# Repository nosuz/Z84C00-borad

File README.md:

# Z80(Z84C00) CPU board

This board is designed for running CP/M.

|Item|Spec|
|:--|:--|
|CPU|Z84C00|
|Memory Size|128KiB|
|CPU Clock|Max. 14MHz|
|Interface|USB|

The USB port is used as a interface to connect with the subsystem that controles a console and disk drives.

|File name|Contents|
|:---------|:---|
|Z8S180.pdf|Circuit drawing(PDF)|
|Z8S180.xlsx|BOM list(Excel)|
|Z8S180.zip|zipped Gerber files|

## References

[Z80マイコンボードの製作](https://tech.nosuz.jp/2016/08/z80-cpu-borad/)

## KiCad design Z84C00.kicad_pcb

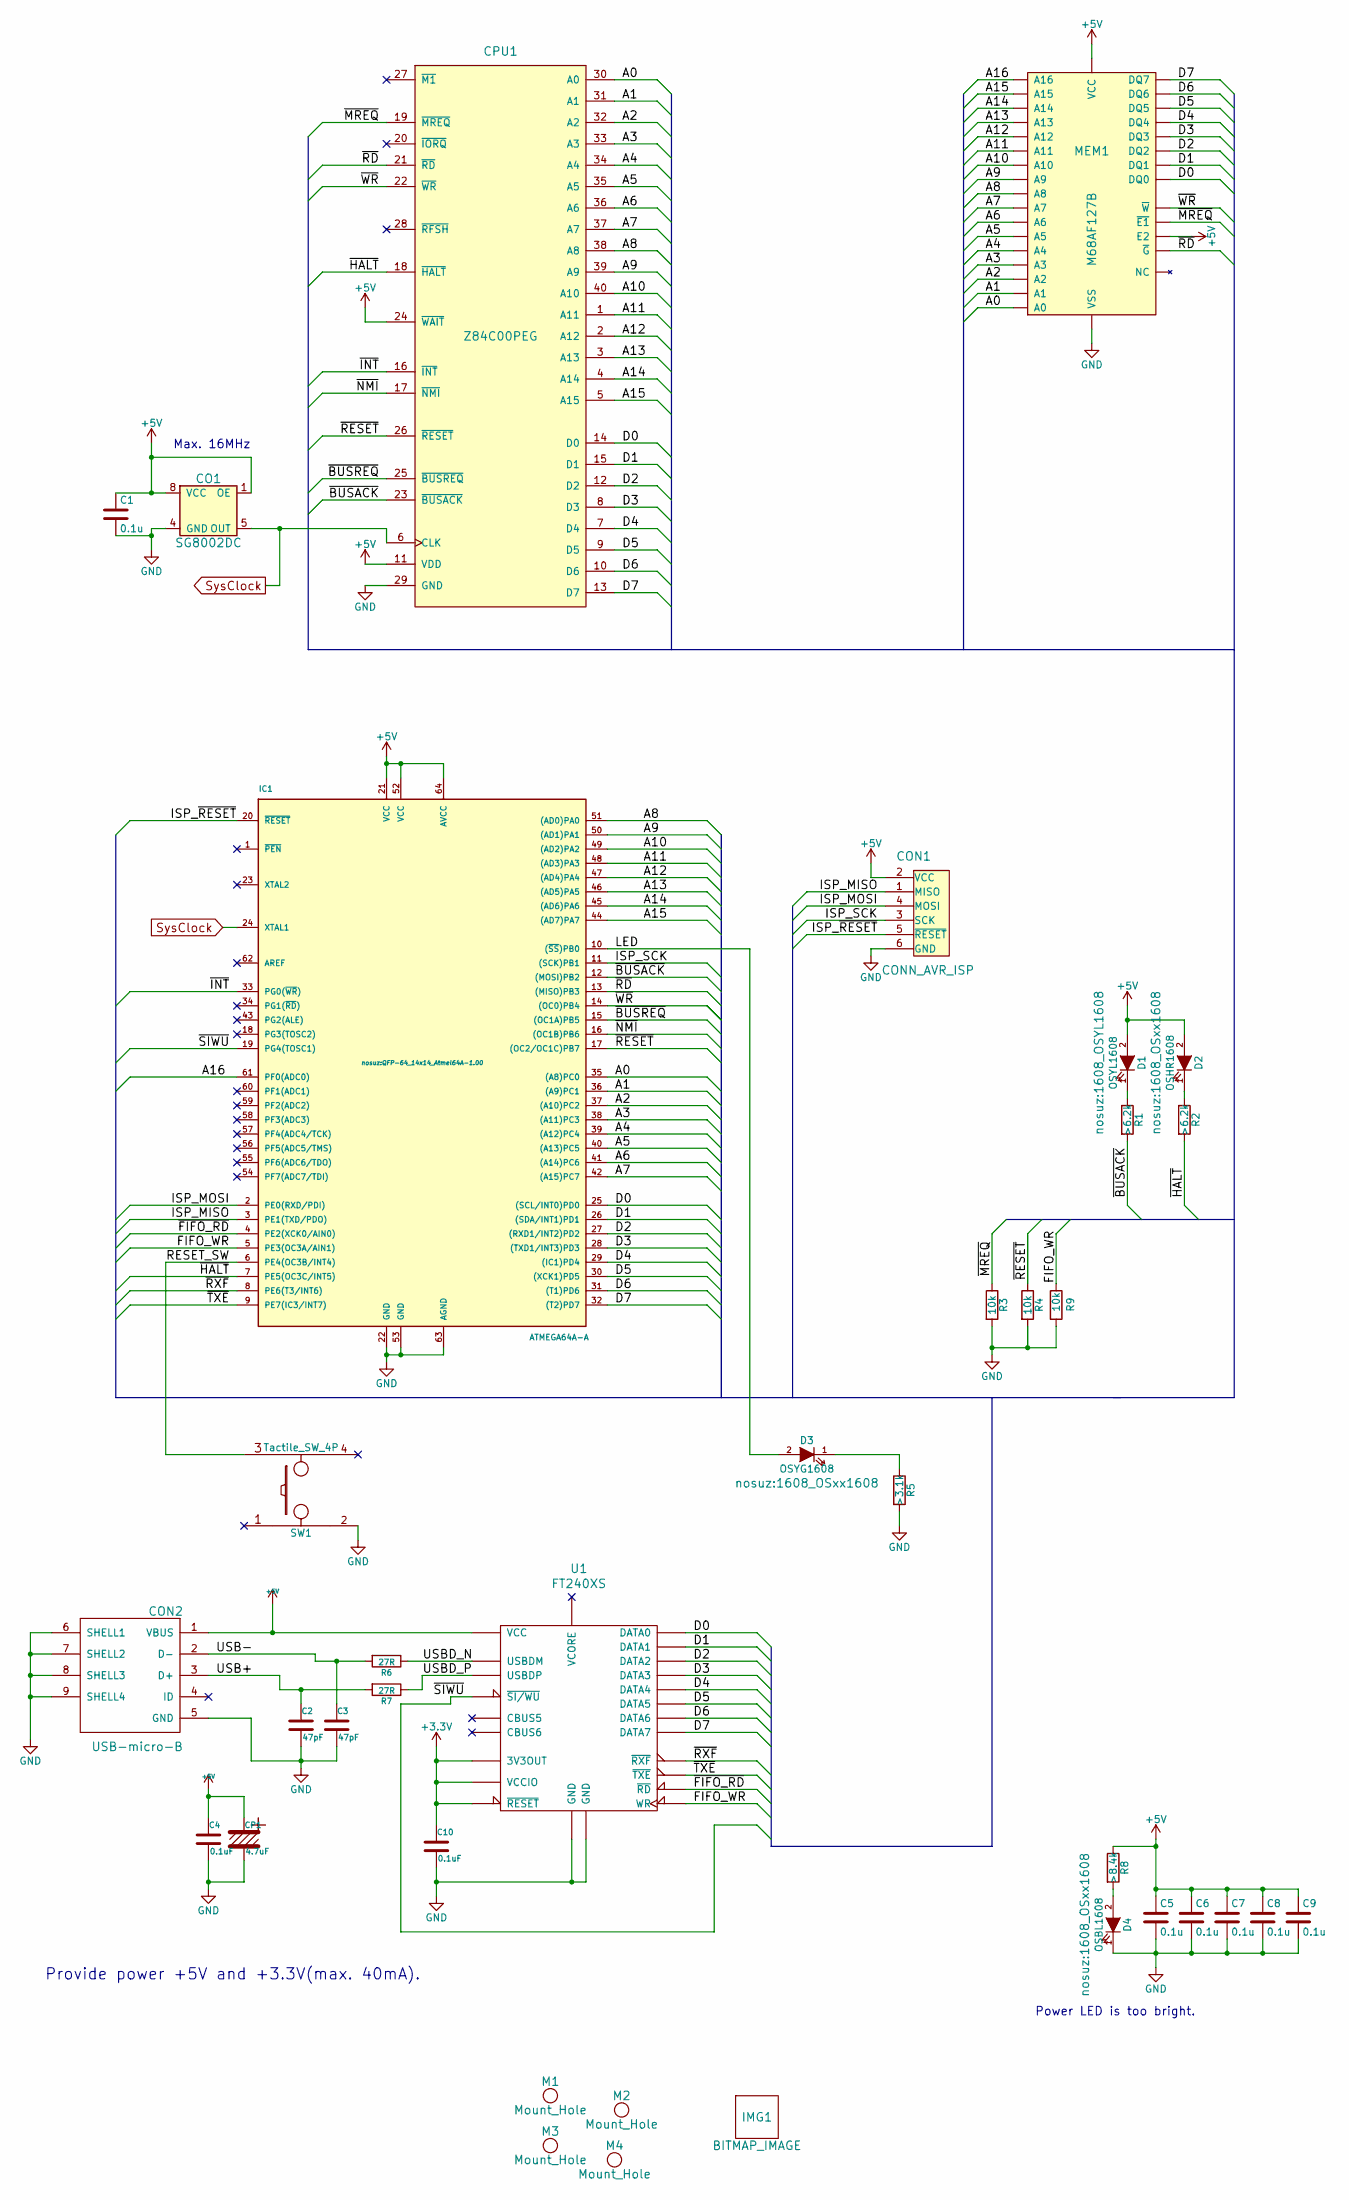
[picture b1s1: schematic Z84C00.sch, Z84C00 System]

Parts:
C1, C5, C6, C7, C8, C9: 0.1u; C_2012
C2, C3: 47pF; C_2012
C4, C10: 0.1uF; C_2012
CO1: SG8002DC; DIP8_2227MC-08
CON1: CONN_AVR_ISP; AVR_ISP_2x03
CON2: USB-micro-B; USB-micro-B_Hirose
CP1: 4.7uF; CP_SMD_D5
CPU1: Z84C00PEG; DIP-40_Z84C00
D1: OSYL1608; 1608_OSYL1608
D2: OSHR1608; 1608_OSxx1608
D3: OSYG1608; 1608_OSxx1608
D4: OSBL1608; 1608_OSxx1608
IC1: ATMEGA64A-A; QFP-64_14x14_Atmel64A-1.00
IMG1: BITMAP_IMAGE; Icon_Nosuz
M1, M2, M3, M4: Mount_Hole; HOLE-M3
MEM1: M68AF127B; SO32_STM_M68AF127B
R1, R2: >6.2k; R_1608
R3, R4, R9: 10k; R_1608
R5: >3.1k; R_1608
R6, R7: 27R; R_1608
R8: >8.4k; R_1608
SW1: Tactile_SW_4P; SKRPACE010
U1: FT240XS; SSOP-24_FT240XS

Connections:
+3V3: C10.1, U1.3 (VCCIO), U1.15 (3V3OUT), U1.16 (~RESET)
+5V: C1.1, C4.1, C5.1, C6.1, C7.1, C8.1, C9.1, CO1.1 (OE), CO1.8 (VCC), CON1.2 (VCC), CON2.1 (VBUS), CP1.1, CPU1.11 (VDD), CPU1.24 (~WAIT), D1.2 (A), D2.2 (A), IC1.21 (VCC), IC1.52 (VCC), IC1.64 (AVCC), MEM1.30 (E2), MEM1.32 (VCC), R8.1, U1.18 (VCC)
/A0: CPU1.30 (A0), IC1.35 ((A8)PC0), MEM1.12 (A0)
/A1: CPU1.31 (A1), IC1.36 ((A9)PC1), MEM1.11 (A1)
/A2: CPU1.32 (A2), IC1.37 ((A10)PC2), MEM1.10 (A2)
/A3: CPU1.33 (A3), IC1.38 ((A11)PC3), MEM1.9 (A3)
/A4: CPU1.34 (A4), IC1.39 ((A12)PC4), MEM1.8 (A4)
/A5: CPU1.35 (A5), IC1.40 ((A13)PC5), MEM1.7 (A5)
/A6: CPU1.36 (A6), IC1.41 ((A14)PC6), MEM1.6 (A6)
/A7: CPU1.37 (A7), IC1.42 ((A15)PC7), MEM1.5 (A7)
/A8: CPU1.38 (A8), IC1.51 ((AD0)PA0), MEM1.27 (A8)
/A9: CPU1.39 (A9), IC1.50 ((AD1)PA1), MEM1.26 (A9)
/A10: CPU1.40 (A10), IC1.49 ((AD2)PA2), MEM1.23 (A10)
/A11: CPU1.1 (A11), IC1.48 ((AD3)PA3), MEM1.25 (A11)
/A12: CPU1.2 (A12), IC1.47 ((AD4)PA4), MEM1.4 (A12)
/A13: CPU1.3 (A13), IC1.46 ((AD5)PA5), MEM1.28 (A13)
/A14: CPU1.4 (A14), IC1.45 ((AD6)PA6), MEM1.3 (A14)
/A15: CPU1.5 (A15), IC1.44 ((AD7)PA7), MEM1.31 (A15)
/A16: IC1.61 (PF0(ADC0)), MEM1.2 (A16)
/D0: CPU1.14 (D0), IC1.25 ((SCL/INT0)PD0), MEM1.13 (DQ0), U1.24 (DATA0)
/D1: CPU1.15 (D1), IC1.26 ((SDA/INT1)PD1), MEM1.14 (DQ1), U1.4 (DATA1)
/D2: CPU1.12 (D2), IC1.27 ((RXD1/INT2)PD2), MEM1.15 (DQ2), U1.2 (DATA2)
/D3: CPU1.8 (D3), IC1.28 ((TXD1/INT3)PD3), MEM1.17 (DQ3), U1.9 (DATA3)
/D4: CPU1.7 (D4), IC1.29 ((IC1)PD4), MEM1.18 (DQ4), U1.1 (DATA4)
/D5: CPU1.9 (D5), IC1.30 ((XCK1)PD5), MEM1.19 (DQ5), U1.7 (DATA5)
/D6: CPU1.10 (D6), IC1.31 ((T1)PD6), MEM1.20 (DQ6), U1.8 (DATA6)
/D7: CPU1.13 (D7), IC1.32 ((T2)PD7), MEM1.21 (DQ7), U1.5 (DATA7)
/FIFO_WR: IC1.5 (PE3(OC3A/AIN1)), R9.1, U1.12 (WR)
/ISP_MISO: CON1.1 (MISO), IC1.3 (PE1(TXD/PDO))
/ISP_MOSI: CON1.4 (MOSI), IC1.2 (PE0(RXD/PDI))
/ISP_SCK: CON1.3 (SCK), IC1.11 ((SCK)PB1)
/ISP_~RESET: CON1.5 (~RESET), IC1.20 (~RESET)
/LED: D3.2 (A), IC1.10 ((~SS~)PB0)
/RESET_SW: IC1.6 (PE4(OC3B/INT4)), SW1.3
/USB+: C2.1, CON2.3 (D+), R7.2
/USB-: C3.1, CON2.2 (D-), R6.2
/USBD_N: R6.1, U1.14 (USBDM)
/USBD_P: R7.1, U1.13 (USBDP)
/~BUSACK: CPU1.23 (~BUSACK), IC1.12 ((MOSI)PB2), R1.2
/~BUSREQ: CPU1.25 (~BUSREQ), IC1.15 ((OC1A)PB5)
/~FIFO_RD: IC1.4 (PE2(XCK0/AIN0)), U1.11 (~RD)
/~HALT: CPU1.18 (~HALT), IC1.7 (PE5(OC3C/INT5)), R2.2
/~INT: CPU1.16 (~INT), IC1.33 (PG0(~WR~))
/~MREQ: CPU1.19 (~MREQ), MEM1.22 (~E1), R3.1
/~NMI: CPU1.17 (~NMI), IC1.16 ((OC1B)PB6)
/~RD: CPU1.21 (~RD), IC1.13 ((MISO)PB3), MEM1.24 (~G)
/~RESET: CPU1.26 (~RESET), IC1.17 ((OC2/OC1C)PB7), R4.1
/~RXF: IC1.8 (PE6(T3/INT6)), U1.21 (~RXF)
/~SIWU: IC1.19 (PG4(TOSC1)), U1.10 (~SI/WU)
/~TXE: IC1.9 (PE7(IC3/INT7)), U1.20 (~TXE)
/~WR: CPU1.22 (~WR), IC1.14 ((OC0)PB4), MEM1.29 (~W)
GND: C1.2, C2.2, C3.2, C4.2, C5.2, C6.2, C7.2, C8.2, C9.2, C10.2, CO1.4 (GND), CON1.6 (GND), CON2.5 (GND), CON2.6 (SHELL1), CON2.7 (SHELL2), CON2.8 (SHELL3), CON2.9 (SHELL4), CP1.2, CPU1.29 (GND), D4.1 (K), IC1.22 (GND), IC1.53 (GND), IC1.63 (AGND), MEM1.16 (VSS), R3.2, R4.2, R5.2, R9.2, SW1.2, U1.6 (GND), U1.19 (GND)
unnamed: D1.1 (K), R1.1
unnamed: D2.1 (K), R2.1
unnamed: D3.1 (K), R5.1
unnamed: D4.2 (A), R8.2
SysClock: CO1.5 (OUT), CPU1.6 (CLK), IC1.24 (XTAL1)

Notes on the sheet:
Provide power +5V and +3.3V(max. 40mA).
Max. 16MHz
Power LED is too bright.

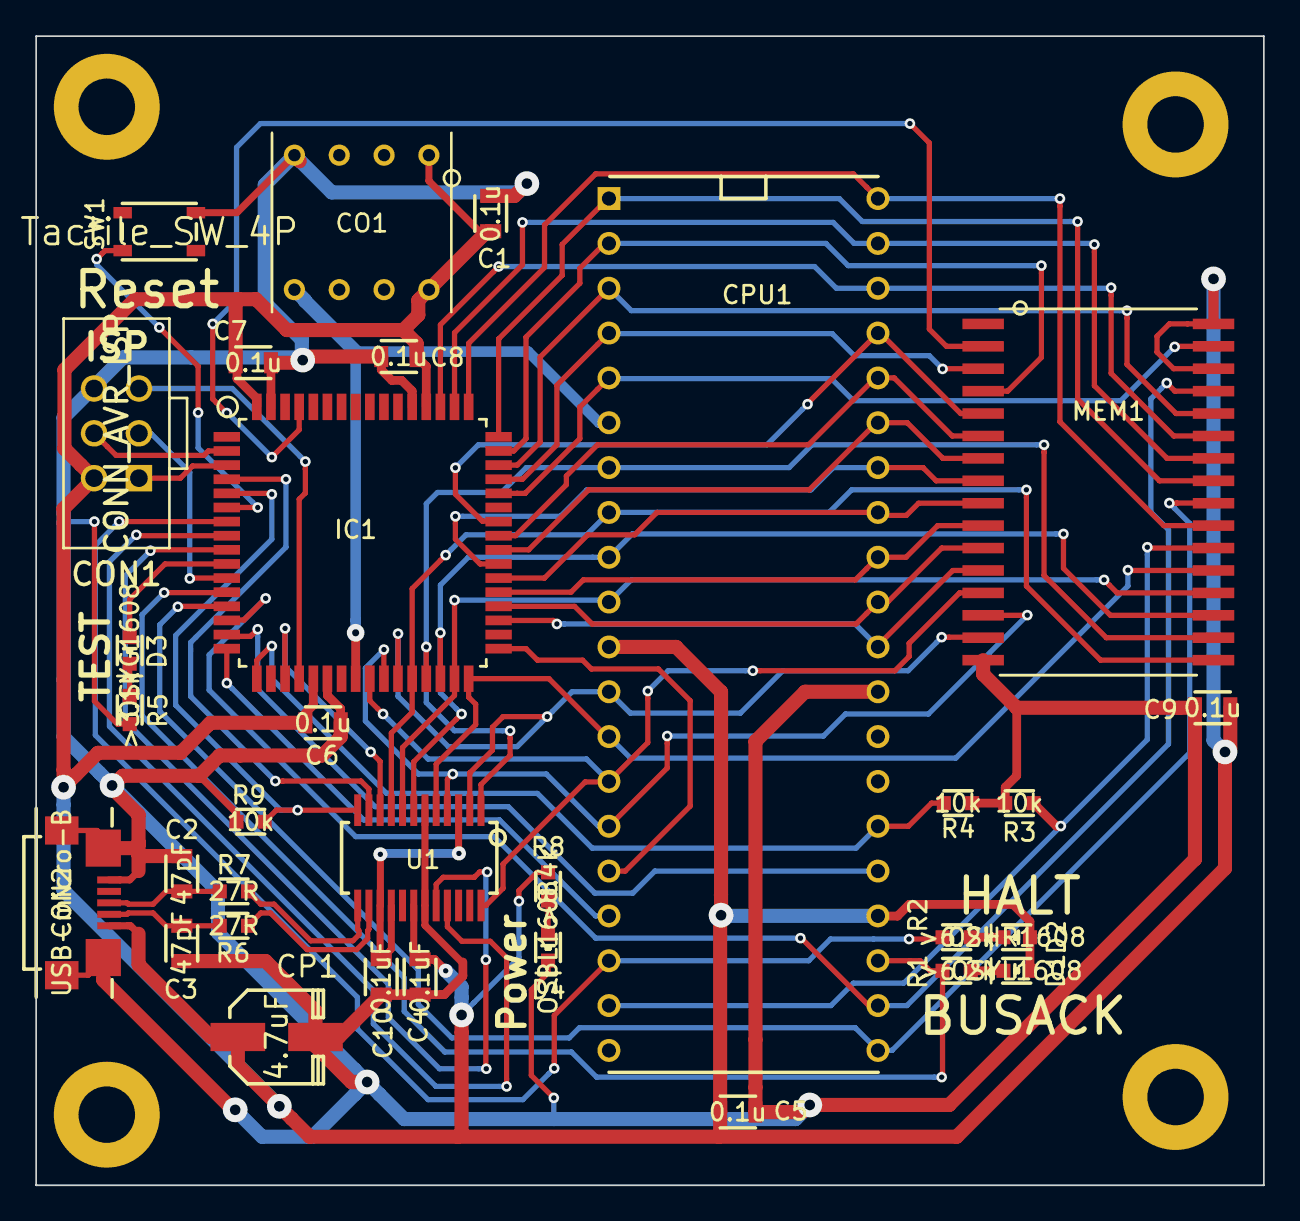
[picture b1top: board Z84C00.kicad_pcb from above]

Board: 2 copper layers, 69.6 x 65.1 mm, 37 parts (1 on the bottom side), 57 nets.

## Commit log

2016-08-24 Added REAME files
2016-08-24 Fixed README table header.
